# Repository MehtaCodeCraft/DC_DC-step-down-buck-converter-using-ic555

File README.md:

# DC_DC-step-down-buck-converter-using-ic555
A DC-DC step-down (buck) converter is a power electronics device that converts a higher input voltage to a lower output voltage efficiently. Here’s a detailed description and common specifications:
Description
Functionality:
•	Buck Converter: The buck converter uses a switching element (typically a transistor) to chop the input voltage and regulate the output voltage through an inductor, diode, and capacitor.
•	Operation Principle: When the switch is on, current flows through the inductor and energy is stored. When the switch is off, the inductor releases energy to the output load. The output voltage is controlled by varying the duty cycle of the switching signal.
Key Specifications
1.	Input Voltage Range (V_in):
o	Typical range: 5V to 60V (varies by model).
2.	Output Voltage (V_out):
o	Adjustable or fixed output, commonly from 1.2V to 30V.
3.	Output Current (I_out):
o	Maximum output current: Generally ranges from a few hundred milliamps to several amps (e.g., 1A, 3A, 5A, or higher).
4.	Efficiency:
o	Efficiency rates often exceed 85% to 95%, depending on load conditions and specific design.
5.	Switching Frequency:
o	Common frequencies: 100 kHz to 1 MHz, impacting size and performance.
6.	Ripple Voltage:
o	Output ripple typically specified in millivolts, important for sensitive applications.
7.	Protection Features:
o	Overcurrent protection
o	Thermal shutdown
o	Input under-voltage lockout (UVLO)
8.	Package Type:
o	Available in various forms including through-hole and surface mount (SMD).
Applications
•	Power supply for microcontrollers and other low-voltage devices
•	Battery-powered devices where efficiency is critical
•	LED drivers
•	DC motor drivers
Example Components
•	Integrated Circuits (ICs): Common examples include the LM2596, LM2675, and TPS54331.
•	Discrete Solutions: Using MOSFETs and external components for custom applications.

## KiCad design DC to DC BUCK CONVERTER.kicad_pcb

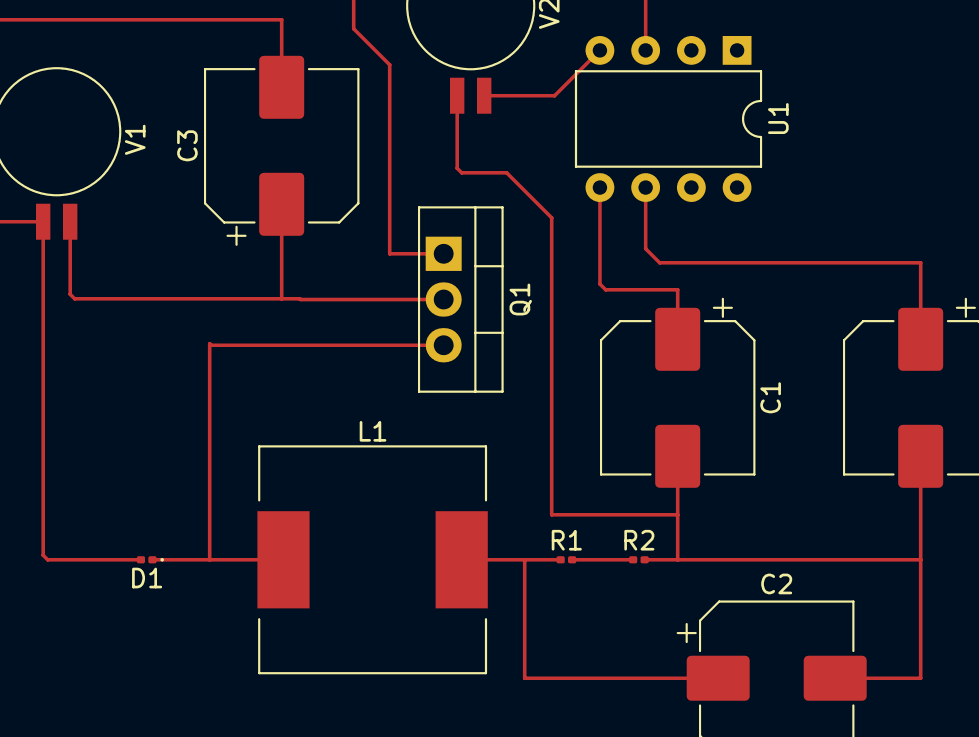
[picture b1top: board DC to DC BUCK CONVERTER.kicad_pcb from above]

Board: 2 copper layers, 12 parts (0 on the bottom side), 8 nets.

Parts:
C1, C4: 10nF; CP_Elec_8x10
C2: 47uF; CP_Elec_8x10
C3: 22uF; CP_Elec_8x10
D1: D_Schottky; D_0201_0603Metric
L1: 33uH; L_12x12mm_H6mm
Q1: IRLZ44N; TO-220-3_Vertical
R1: 1k; R_0201_0603Metric
R2: 10k; R_0201_0603Metric
U1: NE555P; DIP-8_W7.62mm
V1: 24V; BatteryHolder_Seiko_MS621F
V2: 12V; BatteryHolder_Seiko_MS621F

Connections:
/Vout: C2.1, L1.2, R1.1
GND: C1.2, C2.2, C3.2, C4.1, C4.2, D1.2 (A), R2.2, U1.1 (GND), U1.2 (TR), U1.6 (THR), V1.2, V2.2
unnamed: D1.1 (K), L1.1, Q1.3 (S)
unnamed: C3.1, Q1.2 (D), V1.1
unnamed: Q1.1 (G), U1.3 (Q)
unnamed: C1.1, U1.5 (CV)
unnamed: R1.2, R2.1, U1.7 (DIS)
unnamed: U1.4 (R), U1.8 (VCC), V2.1

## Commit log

2024-09-26 README.md
